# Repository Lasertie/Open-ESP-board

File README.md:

# Open ESP Board
# [Le ReadMe est en construction]
## Pourquoi ce projet ?
Le but de cette carte faire un carte ESP32 exclusive pour la domotique. La carte est pensée pou etre "All-proff"
### Histoirex
L' Open ESP Board est né de deux besoins conjoints : Une carte de domotique et une carte multifonction. Mon besoin etait d'avoir une carte domotique current proff, j'avais besoin de pouvoir recevoir un signal éléctique instable et de détecter sa presence. Mais il y avait un autre projet pour Intelli Lab. J'ai donc réunit ces deux besoins pour faire une carte universelle. Malheuresement je n'etait pas expert dans le domaine, mais il me fallait une puce centrale. Donc etant donné la communauté autour de l'ESP32, je me suis tourné vers cette puce.
### La philosophie

## Licence
Ce projet est sous la LOC. Voir [loc.zyglonk.fr](https://loc.zyglonk.fr) pour plus de détails.

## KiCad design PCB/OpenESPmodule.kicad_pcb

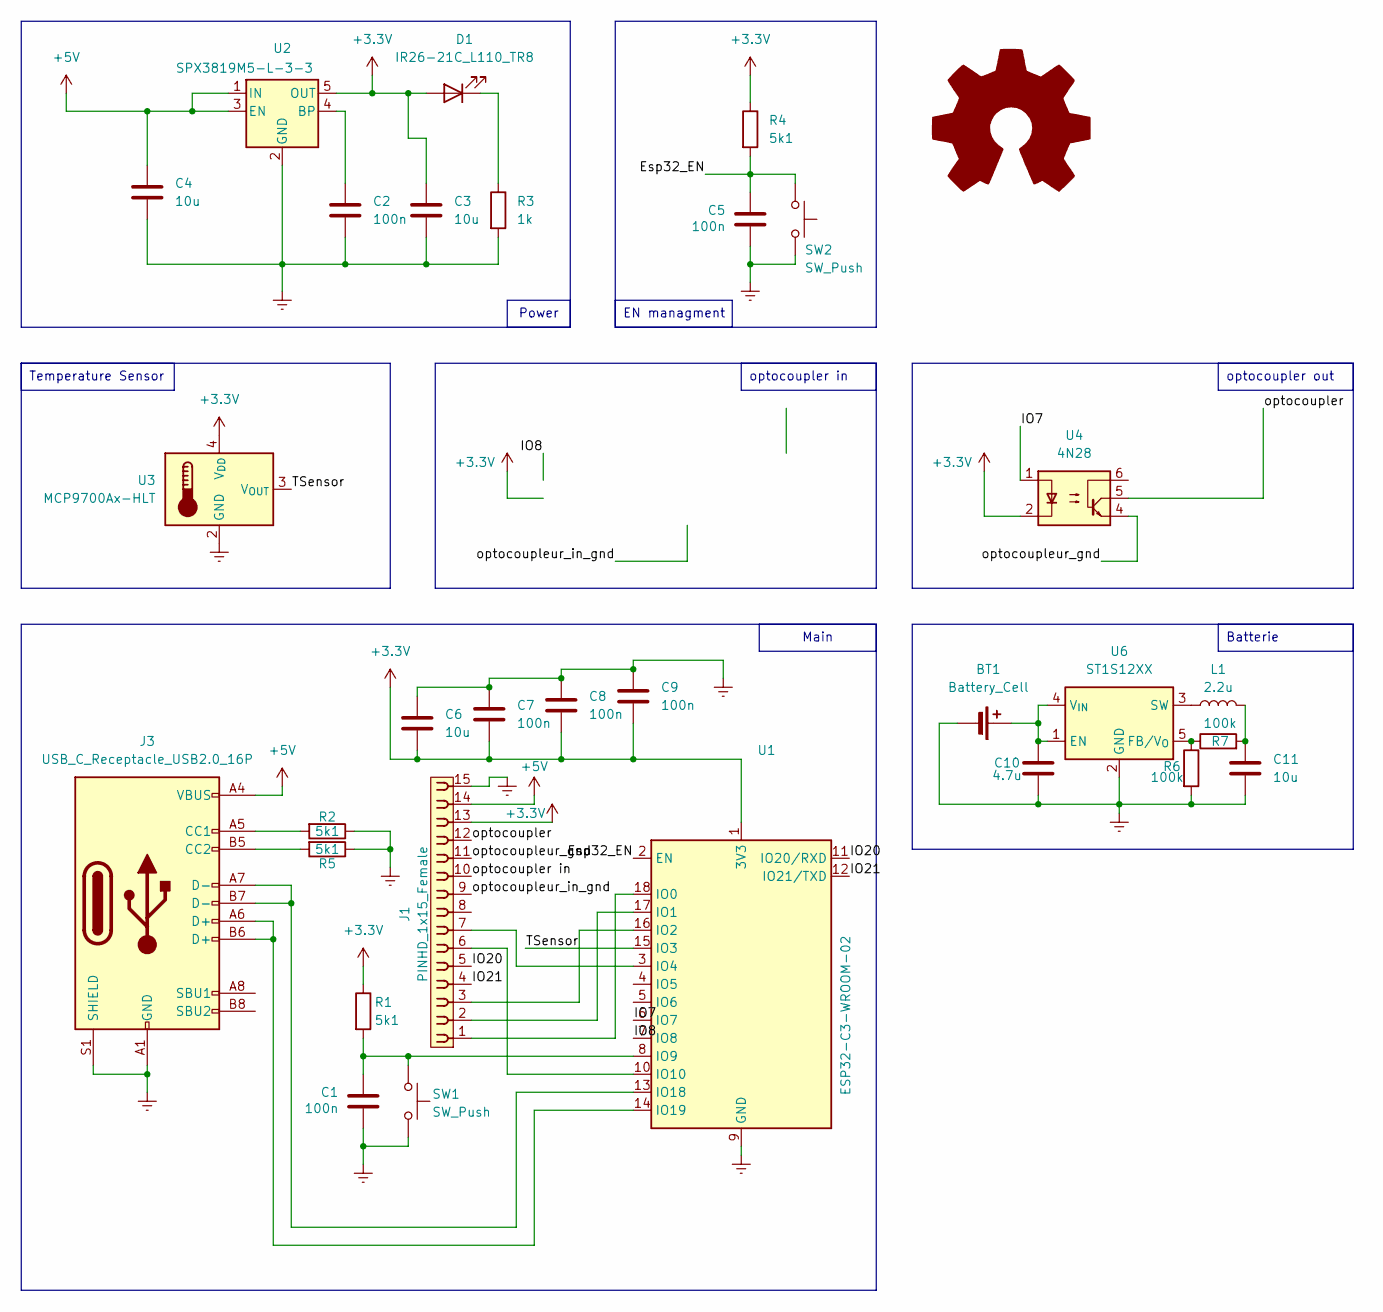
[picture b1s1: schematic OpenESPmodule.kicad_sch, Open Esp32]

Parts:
BT1: Battery_Cell; BatteryHolder_Keystone_1060_1x2032
C1, C2, C5, C7, C8, C9: 100n; C_0201_0603Metric
C3, C4, C6: 10u; C_0201_0603Metric
C10: 4.7u; C_0201_0603Metric
C11: 10u
D1: IR26-21C_L110_TR8; LED_1206_3216Metric_Pad1.42x1.75mm_HandSolder
J1: PINHD_1x15_Female; PinSocket_1x15_P2.54mm_Vertical
J3: USB_C_Receptacle_USB2.0_16P; USB_C_Receptacle_GCT_USB4085
L1: 2.2u; L_0201_0603Metric
R1, R2, R4, R5: 5k1; R_0201_0603Metric
R3: 1k; R_0201_0603Metric
R6, R7: 100k; R_0201_0603Metric
SW1, SW2: SW_Push; SW_DIP_SPSTx01_Slide_9.78x4.72mm_W7.62mm_P2.54mm
U1: ESP32-C3-WROOM-02
U2: SPX3819M5-L-3-3; SOT-23-5
U3: MCP9700Ax-HLT; SOT-353_SC-70-5
U4: 4N28; DIP-6_W7.62mm
U6: ST1S12XX; TSOT-23-5

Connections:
+3.3V: C3.1, C6.2, C7.2, C8.2, C9.2, D1.2 (A), J1.13, R1.1, R4.1, U1.1 (3V3), U2.5 (OUT), U3.4 (V_{DD}), U4.2
+5V: C4.1, J1.14, J3.A4 (VBUS), J3.A9 (VBUS), J3.B4 (VBUS), J3.B9 (VBUS), U2.1 (IN), U2.3 (EN)
/Esp32_EN: C5.1, R4.2, SW2.1, U1.2 (EN)
/IO7: U1.6 (IO7), U4.1
/IO8: U1.7 (IO8)
/IO20: J1.5, U1.11 (IO20/RXD)
/IO21: J1.4, U1.12 (IO21/TXD)
/TSensor: U1.15 (IO3), U3.3 (V_{OUT})
/optocoupler: J1.12, U4.5
/optocoupler in: J1.10
/optocoupleur_gnd: J1.11, U4.4
/optocoupleur_in_gnd: J1.9
Earth: BT1.2 (-), C1.2, C2.2, C3.2, C4.2, C5.2, C6.1, C7.1, C8.1, C9.1, C10.2, C11.2, J1.15, J3.A1 (GND), J3.A12 (GND), J3.B1 (GND), J3.B12 (GND), J3.S1 (SHIELD), R2.1, R3.2, R5.1, R6.2, SW1.2, SW2.2, U1.9 (GND), U1.19 (GND), U2.2 (GND), U3.2 (GND), U6.2 (GND)
unnamed: BT1.1 (+), C10.1, U6.1 (EN), U6.4 (V_{IN})
unnamed: C11.1, L1.2, R7.2
unnamed: D1.1 (K), R3.1
unnamed: J3.A5 (CC1), R2.2
unnamed: J3.B5 (CC2), R5.2
unnamed: J1.1, U1.18 (IO0)
unnamed: J1.2, U1.17 (IO1)
unnamed: J1.3, U1.16 (IO2)
unnamed: J1.7, U1.3 (IO4)
unnamed: C1.1, R1.2, SW1.1, U1.8 (IO9)
unnamed: J1.6, U1.10 (IO10)
unnamed: J3.A7 (D-), J3.B7 (D-), U1.13 (IO18)
unnamed: J3.A6 (D+), J3.B6 (D+), U1.14 (IO19)
unnamed: C2.1, U2.4 (BP)
unnamed: R6.1, R7.1, U6.5 (FB/V_{O})
unnamed: L1.1, U6.3 (SW)

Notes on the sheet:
Power
Temperature Sensor
EN managment
optocoupler in
Main
optocoupler out
Batterie

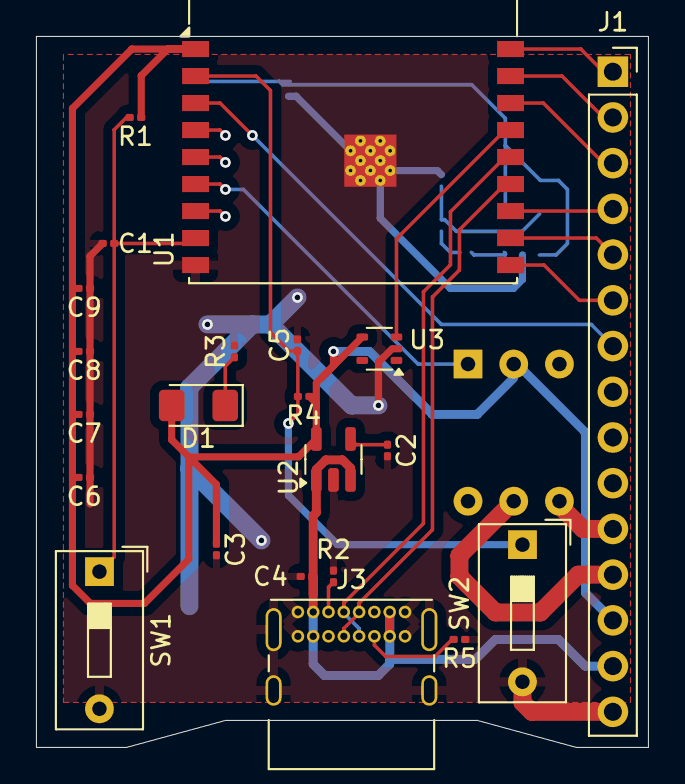
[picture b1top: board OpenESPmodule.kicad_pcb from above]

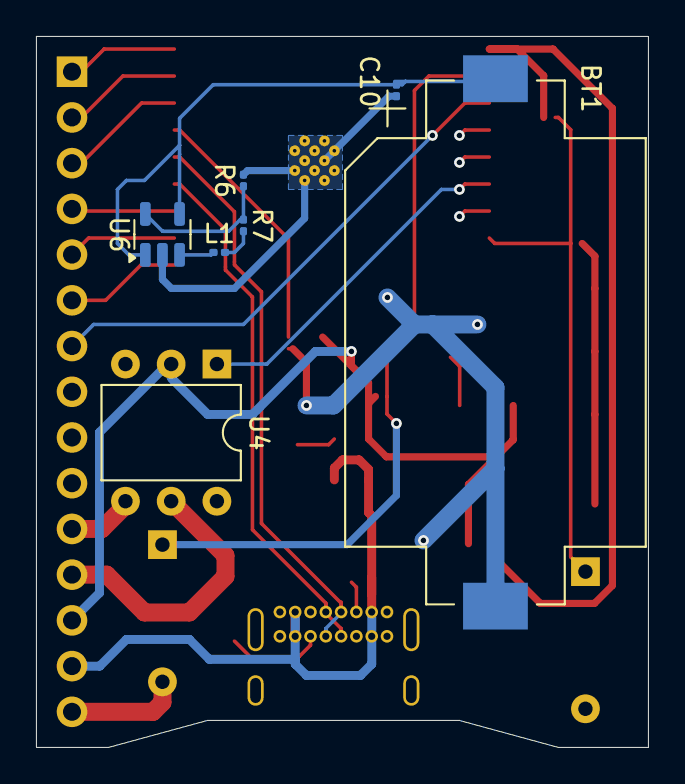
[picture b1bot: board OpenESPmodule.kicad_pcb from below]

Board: 2 copper layers, 34.0 x 39.5 mm, 29 parts (7 on the bottom side), 26 nets.

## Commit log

2025-04-07 init
2025-04-07 readme maj
2025-04-07 readme add license
2025-04-22 ajout de la fermeture
2025-05-02 new box version
2025-05-06 ammelioration de la carte + Update README
2025-05-06 Add power managment

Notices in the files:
PCB/OpenESPmodule.kicad_sch:
Licence : LOC (loc.zyglonk.fr)
